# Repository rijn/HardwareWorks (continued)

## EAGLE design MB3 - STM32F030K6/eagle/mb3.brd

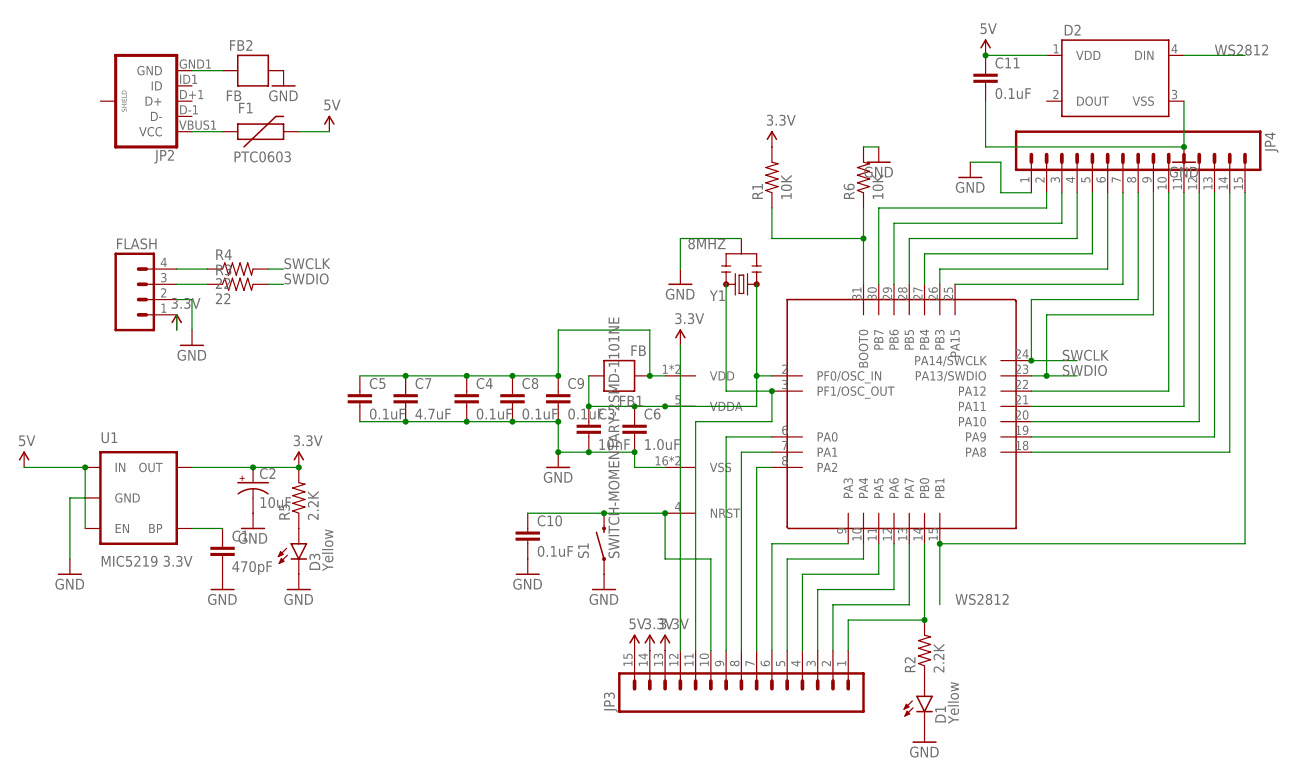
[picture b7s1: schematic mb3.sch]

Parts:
C1: 470pF; 0402-CAP
C2: 10uF; EIA3216
C3: 10nF; 0402-CAP
C4, C5, C8, C9, C10, C11: 0.1uF; 0402-CAP
C6: 1.0uF; 0603-CAP
C7: 4.7uF; 0603-CAP
D1, D3: Yellow; LED-0603
D2: WS2812B
F1: PTC0603; 0603
FB1, FB2: FB; 0603
FLASH: M04SMD; 1X04-SMD
JP2: USB_MICROB_PLUGCONN-11752; USB-B-MICRO-SMD_V03
JP3, JP4: M15LOCK; 1X15_LOCK
R1, R6: 10K; 0402-RES
R2, R5: 2.2K; 0402-RES
R3, R4: 22; 0402-RES
S1: SWITCH-MOMENTARY-2SMD-1101NE; TACTILE-SWITCH-1101NE
U1: MIC5219 3.3V; SOT23-5
U2: STM32F030K6P6; LQFP32-0.8
Y1: 8MHZ; RESONATOR-SMD

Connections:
3.3V: C2.A (+), C3.1, C6.1, FB1.1, FLASH.1, JP3.13, JP3.14, R1.2, R5.2, U1.5 (OUT), U2.5 (VDDA)
5V: C11.1, D2.1 (VDD), F1.2, JP3.15, U1.1 (IN), U1.3 (EN)
A15: JP4.7, U2.25 (PA15)
COPOY: C1.2, C2.C (-), C3.2, C4.2, C5.2, C6.2, C7.2, C8.2, C9.2, C10.2, C11.2, D1.C, D2.3 (VSS), D3.C, FB2.1, FLASH.2, JP4.1, R6.2, S1.1, U1.2 (GND), U2.16 (VSS), U2.32 (VSS), Y1.2
unnamed: C4.1, C5.1, C7.1, C8.1, C9.1, FB1.2, U2.1 (VDD), U2.17 (VDD)
unnamed: C1.1, U1.4 (BP)
unnamed: FLASH.3, R3.1
unnamed: FLASH.4, R4.1
unnamed: D1.A, R2.1
unnamed: R1.1, R6.1, U2.31 (BOOT0)
unnamed: FB2.2, JP2.GND1 (GND)
unnamed: F1.1, JP2.VBUS1 (VCC)
unnamed: JP4.2, U2.30 (PB7)
unnamed: JP4.3, U2.29 (PB6)
unnamed: JP4.4, U2.28 (PB5)
unnamed: JP4.5, U2.27 (PB4)
unnamed: JP4.6, U2.26 (PB3)
unnamed: JP4.10, U2.22 (PA12)
unnamed: JP4.11, U2.21 (PA11)
unnamed: JP4.12, U2.20 (PA10)
unnamed: JP4.13, U2.19 (PA9)
unnamed: JP4.14, U2.18 (PA8)
unnamed: JP3.2, U2.13 (PA7)
unnamed: JP3.3, U2.12 (PA6)
unnamed: JP3.4, U2.11 (PA5)
unnamed: JP3.5, U2.10 (PA4)
unnamed: JP3.6, U2.9 (PA3)
unnamed: JP3.7, U2.8 (PA2)
unnamed: JP3.8, U2.7 (PA1)
unnamed: JP3.9, U2.6 (PA0)
unnamed: D3.A, R5.1
NRST: C10.1, JP3.10, S1.2, U2.4 (NRST)
PB0: JP3.1, R2.2, U2.14 (PB0)
PF0: JP3.12, U2.2 (PF0/OSC_IN), Y1.1
PF1: JP3.11, U2.3 (PF1/OSC_OUT), Y1.3
SWCLK: JP4.8, R4.2, U2.24 (PA14/SWCLK)
SWDIO: JP4.9, R3.2, U2.23 (PA13/SWDIO)
WS2812: D2.4 (DIN), JP4.15, U2.15 (PB1)

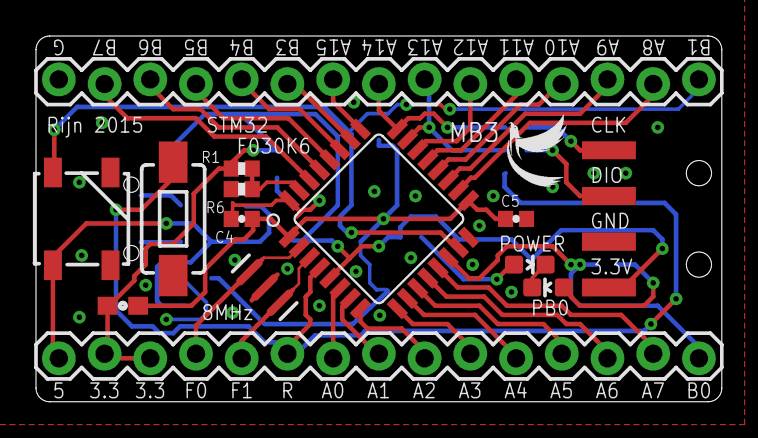
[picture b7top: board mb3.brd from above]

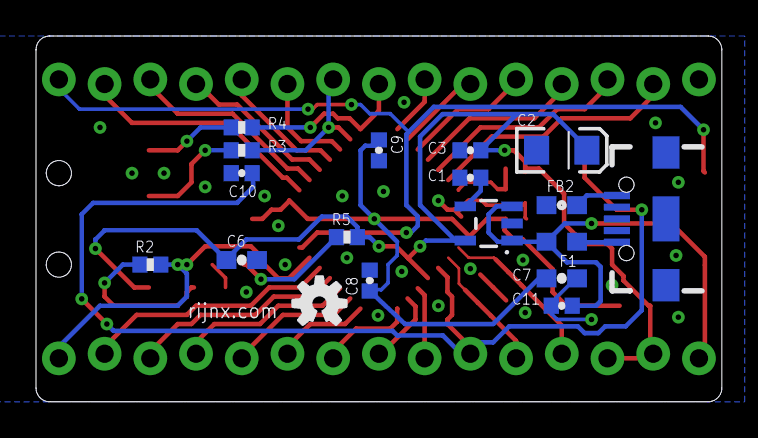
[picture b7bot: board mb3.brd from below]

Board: 2 copper layers, 38.1 x 20.3 mm, 33 parts (18 on the bottom side), 38 nets.

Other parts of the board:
U$1: LOGO
U$2: OSHW-LOGO-S

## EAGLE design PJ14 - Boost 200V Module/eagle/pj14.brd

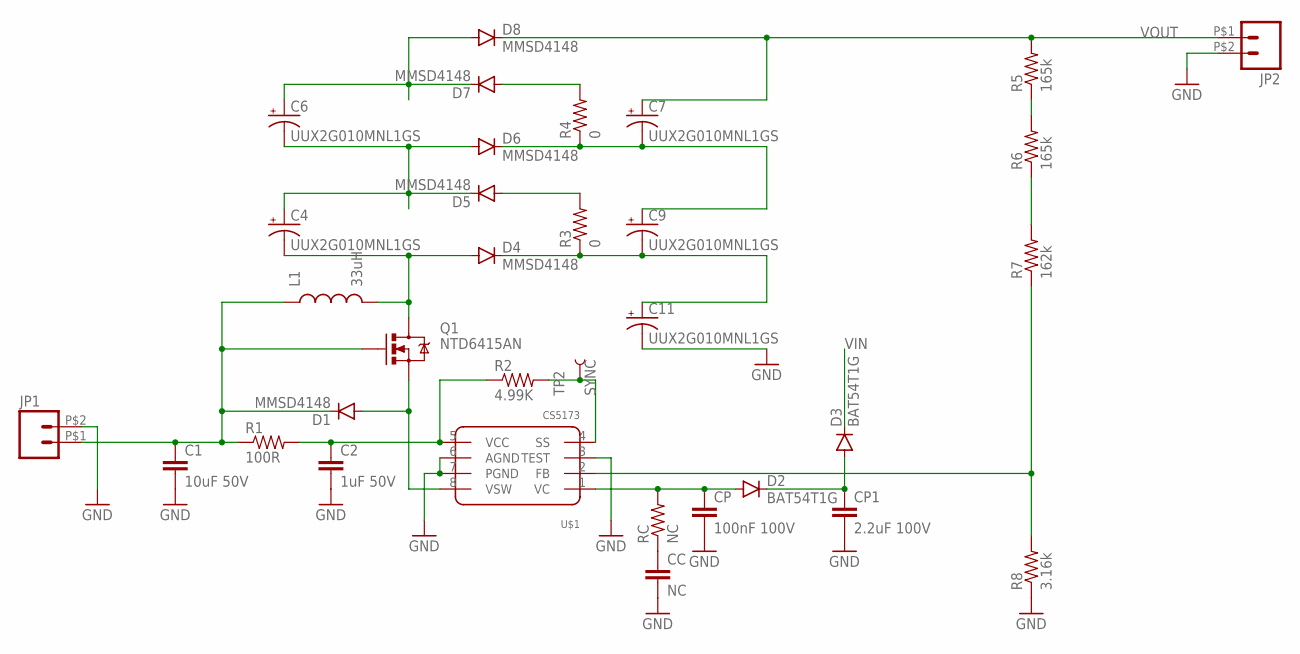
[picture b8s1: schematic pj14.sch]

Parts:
C1: 10uF 50V; 1210
C2: 1uF 50V; 1210
C4, C6, C7, C9, C11: UUX2G010MNL1GS; PANASONIC_E
CC: NC; 0603-CAP
CP: 100nF 100V; 0603-CAP
CP1: 2.2uF 100V; 1210
D1, D4, D5, D6, D7, D8: MMSD4148; SOD-123
D2, D3: BAT54T1G; SOD-123
JP1, JP2: M02; 1X02_5.08
L1: 33uH; CDRH125
Q1: NTD6415AN; DPAK
R1: 100R; 0603-RES
R2: 4.99K; 0603-RES
R3, R4: 0; 0603-RES
R5, R6: 165k; 0603-RES
R7: 162k; 0603-RES
R8: 3.16k; 0603-RES
RC: NC; 0603-RES
TP2: SYNC; PAD.03X.03
U$1: CS5173; SOIC−8

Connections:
GND: C1.2, C2.2, C11.-, CC.2, CP.2, CP1.2, JP1.P$2 (2), JP2.P$2 (2), R8.1, U$1.3 (TEST), U$1.6 (AGND), U$1.7 (PGND)
unnamed: CC.1, RC.1
unnamed: C2.1, R1.2, R2.1, U$1.5 (VCC)
unnamed: D1.A, Q1.3 (S), U$1.8 (VSW)
unnamed: C4.-, D4.A, L1.2, Q1.4 (D)
unnamed: R2.2, TP2.P$1, U$1.4 (SS)
unnamed: CP.1, D2.A, RC.2, U$1.1 (VC)
unnamed: R7.1, R8.2, U$1.2 (FB)
unnamed: CP1.1, D2.C, D3.A
unnamed: D5.A, R3.2
unnamed: C9.-, C11.+, D4.C, R3.1
unnamed: C4.+, C6.-, D5.C, D6.A
unnamed: C6.+, D7.C, D8.A
unnamed: D7.A, R4.2
unnamed: C7.-, C9.+, D6.C, R4.1
unnamed: R5.1, R6.2
unnamed: R6.1, R7.2
VIN: C1.1, D1.C, D3.C, JP1.P$1 (1), L1.1, Q1.1 (G), R1.1
VOUT: C7.+, D8.C, JP2.P$1 (1), R5.2

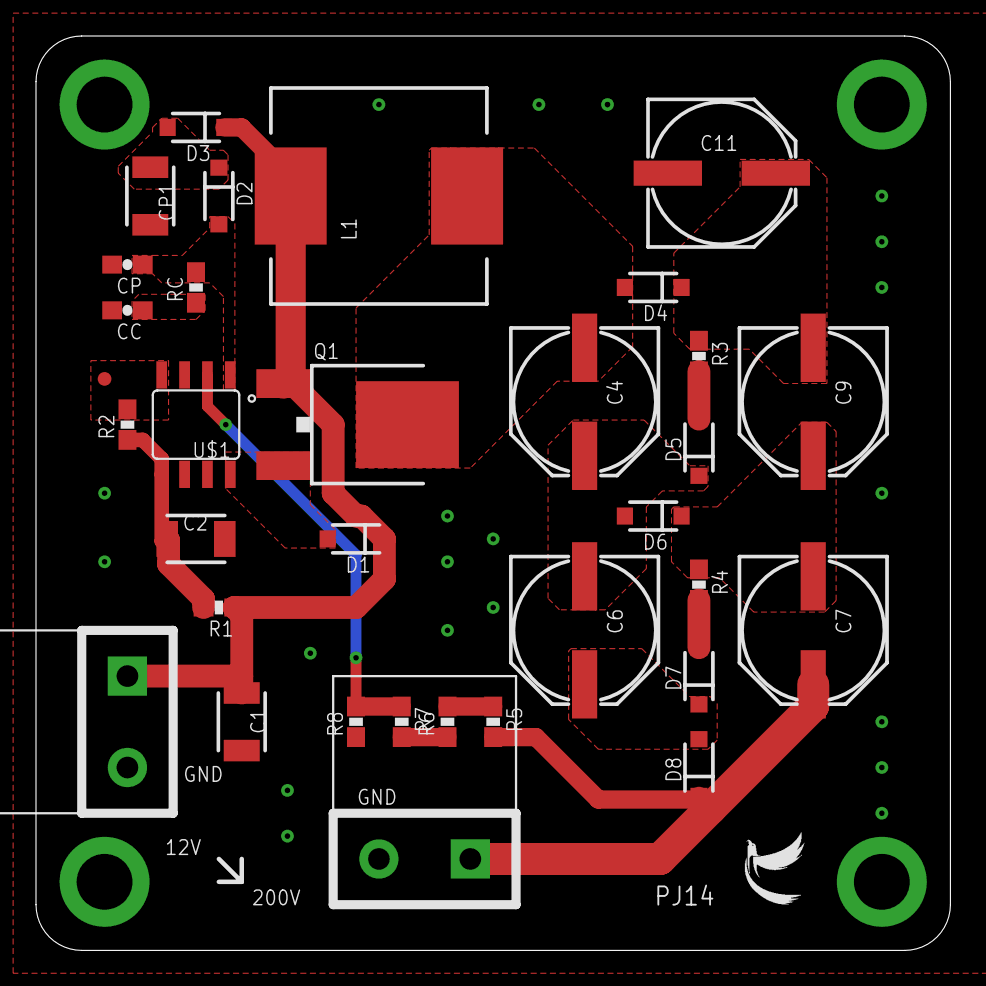
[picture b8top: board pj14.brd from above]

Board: 2 copper layers, 50.8 x 50.8 mm, 35 parts (1 on the bottom side), 19 nets.

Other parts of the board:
U$2: LOGO
U$3: ESD_10.00

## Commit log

2015-08-29 no message
2015-10-15 patch logo file
2015-10-15 alter folder name
2015-11-05 bak Nov 5
2015-12-06 update pj13 & pj15
2016-04-21 some changes
